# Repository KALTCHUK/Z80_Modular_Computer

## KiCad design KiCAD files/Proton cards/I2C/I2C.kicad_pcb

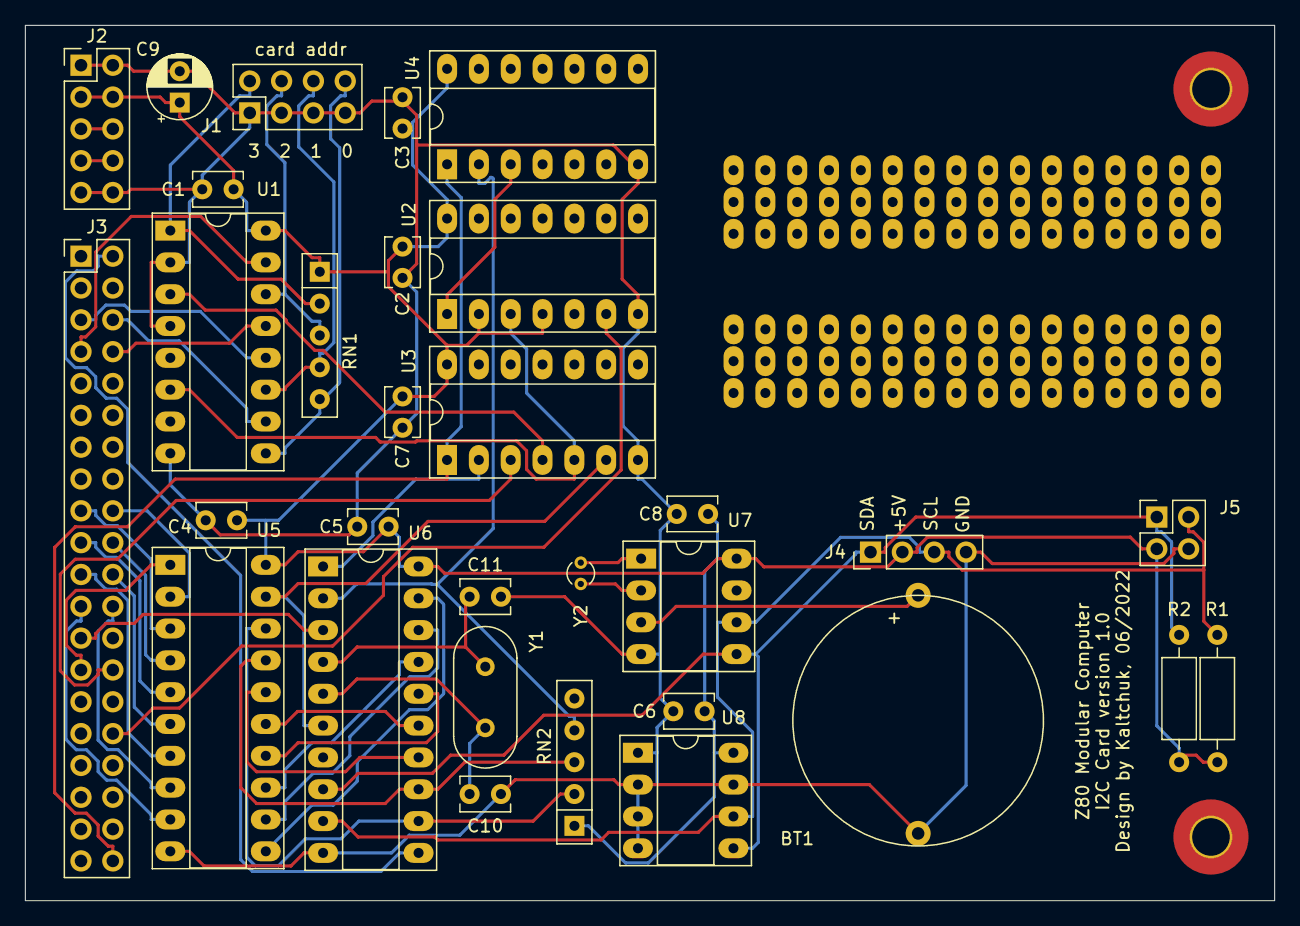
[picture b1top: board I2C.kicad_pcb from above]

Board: 2 copper layers, 99.7 x 69.8 mm, 33 parts (0 on the bottom side), 47 nets.

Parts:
BT1: 3V; Battery-Holder_CR2032
C1, C2, C3, C4, C5, C6, C7, C8: 10nF; C_Disc_D3.8mm_W2.6mm_P2.50mm
C9: 10uF; CP_Radial_D5.0mm_P2.50mm
C10, C11: 33pF; C_Disc_D3.8mm_W2.6mm_P2.50mm
H1, H2: MountingHole; MountingHole_3mm_Pad_TopBottom
J1: card addr; PinHeader_2x04_P2.54mm_Vertical
J2: Power Bus; PinHeader_2x05_P2.54mm_Vertical
J3: Signal Bus; PinHeader_2x20_P2.54mm_Vertical
J4: I2C int; PinHeader_1x04_P2.54mm_Vertical
J5: I2C ext; PinHeader_2x02_P2.54mm_Vertical
R1, R2: 6k8; R_Axial_DIN0207_L6.3mm_D2.5mm_P10.16mm_Horizontal
RN1, RN2: 4x10k; R_Array_SIP5
U1: 74LS85; DIP-16_W7.62mm_Socket_LongPads
U2: 74LS74; DIP-14_W7.62mm_Socket_LongPads
U3: 74LS04; DIP-14_W7.62mm_Socket_LongPads
U4: 74LS08; DIP-14_W7.62mm_Socket_LongPads
U5: 74LS245; DIP-20_W7.62mm_Socket_LongPads
U6: AT89C4051-24P; DIP-20_W7.62mm_Socket_LongPads
U7: DS1307+; DIP-8_W7.62mm_Socket_LongPads
U8: FM24C64B; DIP-8_W7.62mm_Socket_LongPads
Y1: 24MHz; Crystal_HC49-U_Vertical
Y2: 32.768kHz; Crystal_Round_D1.5mm_Vertical

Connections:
+5V: C1.1, C2.1, C3.1, C4.1, C5.1, C6.1, C7.1, C8.1, C9.1, J2.3, J2.4, J4.2, J5.3, R1.2, R2.2, RN1.1 (common), RN2.1 (common), U1.16 (VCC), U2.2 (D), U2.4 (~S), U2.14 (VCC), U3.14 (VCC), U4.14 (VCC), U5.20 (VCC), U6.20 (VCC), U7.8 (VCC), U8.8 (VDD)
+12V: J2.5, J2.6
+BATT: BT1.1 (+), U7.3 (VBAT)
/B00: RN2.2 (R1), U5.18 (B0), U6.12 (P1.0)
/B01: RN2.3 (R2), U5.17 (B1), U6.13 (P1.1)
/B02: U5.16 (B2), U6.14 (P1.2)
/B03: U5.15 (B3), U6.15 (P1.3)
/B04: U5.14 (B4), U6.16 (P1.4)
/B05: U5.13 (B5), U6.17 (P1.5)
/B06: U5.12 (B6), U6.18 (P1.6)
/B07: U5.11 (B7), U6.19 (P1.7)
/SCL: J4.3, J5.2, R1.1, U6.9 (P3.5), U7.6 (SCL), U8.6 (SCL)
/SDA: J4.1, J5.1, R2.1, U6.8 (P3.4), U7.5 (SDA), U8.5 (SDA)
/a00: J3.2, U6.11 (P3.7)
/a04: J3.6, U1.10 (A0)
/a05: J3.5, U1.12 (A1)
/a06: J3.8, U1.13 (A2)
/a07: J3.7, U1.15 (A3)
/card_sel: U1.6 (Oa=b), U2.3 (C), U3.5
/d00: J3.18, U5.2 (A0)
/d01: J3.17, U5.3 (A1)
/d02: J3.20, U5.4 (A2)
/d03: J3.19, U5.5 (A3)
/d04: J3.22, U5.6 (A4)
/d05: J3.21, U5.7 (A5)
/d06: J3.24, U5.8 (A6)
/d07: J3.23, U5.9 (A7)
/iorq: J3.28, U3.3
/rd: J3.27, U5.1 (A->B)
/reset: J3.40, U3.1, U4.1
/v1: J2.7, J2.8
/wait: J3.32, U2.6 (~Q)
/wr: J3.25, U6.3 (P3.1)
GND: BT1.2 (-), C1.2, C2.2, C3.2, C4.2, C5.2, C6.2, C7.2, C8.2, C9.2, C10.2, C11.2, J1.1, J1.3, J1.5, J1.7, J2.1, J2.2, J2.9, J2.10, J4.4, J5.4, U1.2 (Ia<b), U1.4 (Ia>b), U1.8 (GND), U2.7 (GND), U3.7 (GND), U4.7 (GND), U5.10 (GND), U6.10 (GND), U7.4 (GND), U8.1 (A0), U8.2 (A1), U8.3 (A2), U8.4 (VSS), U8.7 (WP)
unnamed: C10.1, U6.5 (XTAL1), Y1.2
unnamed: C11.1, U6.4 (XTAL2), Y1.1
unnamed: J1.2, RN1.2 (R1), U1.1 (B3)
unnamed: J1.4, RN1.3 (R2), U1.14 (B2)
unnamed: J1.6, RN1.4 (R3), U1.11 (B1)
unnamed: J1.8, RN1.5 (R4), U1.9 (B0)
unnamed: RN2.4 (R3), U4.2, U6.2 (P3.0)
unnamed: U1.3 (Ia=b), U3.4
unnamed: U2.1 (~R), U4.3
unnamed: U3.2, U6.1 (RST/VPP)
unnamed: U3.6, U5.19 (CE), U6.6 (P3.2)
unnamed: U7.1 (X1), Y2.2
unnamed: U7.2 (X2), Y2.1

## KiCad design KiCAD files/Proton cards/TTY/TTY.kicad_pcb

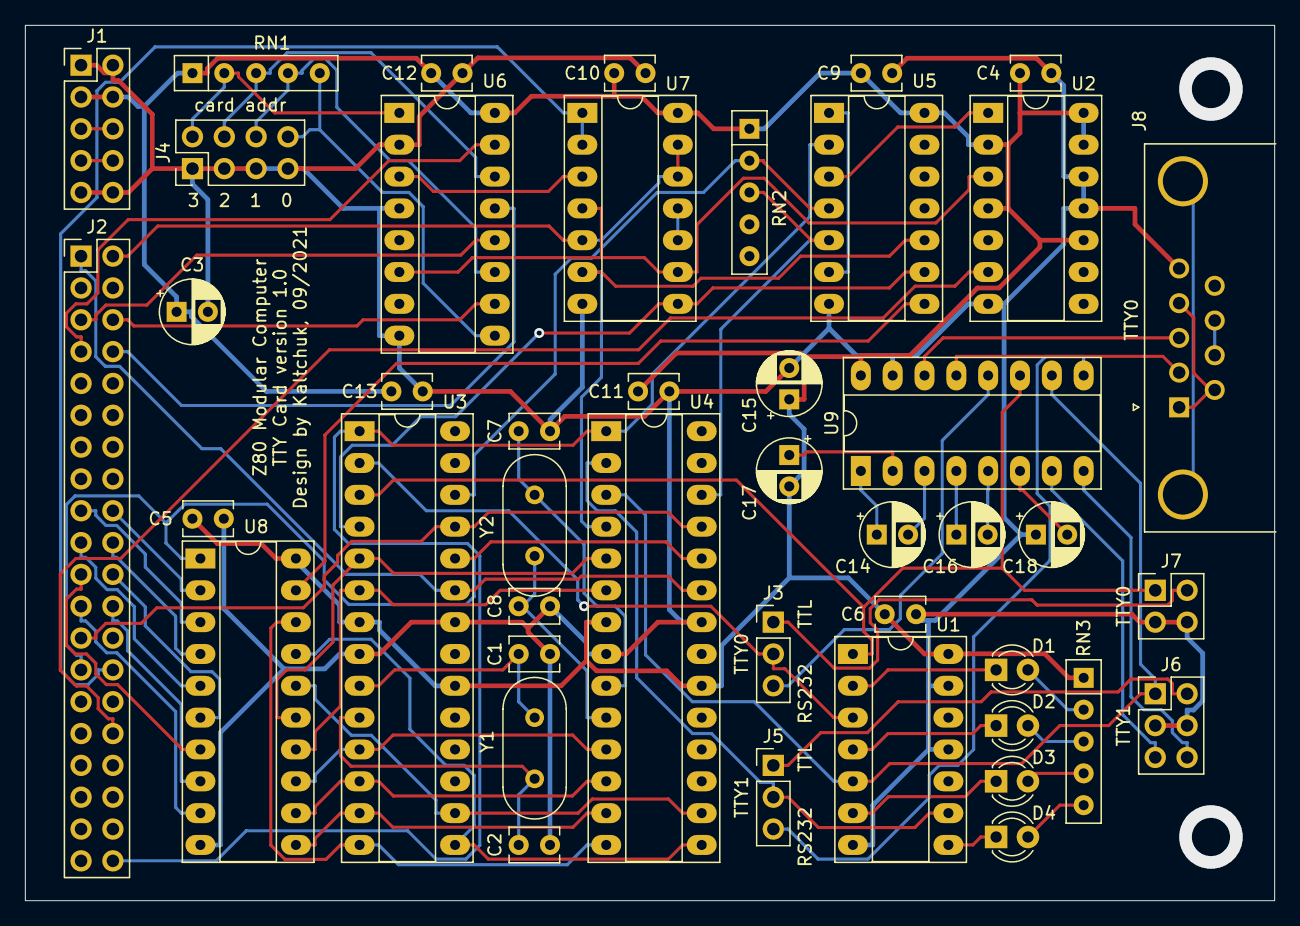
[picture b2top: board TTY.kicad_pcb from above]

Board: 2 copper layers, 99.7 x 69.9 mm, 44 parts (0 on the bottom side), 77 nets.

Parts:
C1, C2, C7, C8: 22pF; C_Disc_D3.8mm_W2.6mm_P2.50mm
C3: 10uF; CP_Radial_D5.0mm_P2.50mm
C4, C5, C6, C9, C10, C11, C12, C13: 10nF; C_Disc_D3.8mm_W2.6mm_P2.50mm
C14, C15, C16, C17, C18: 1uF; CP_Radial_D5.0mm_P2.50mm
D1, D2, D3, D4: LED; LED_D3.0mm
J1: Power Bus; PinHeader_2x05_P2.54mm_Vertical
J2: Signal Buss; PinHeader_2x20_P2.54mm_Vertical
J3, J5: TTL/RS232; PinHeader_1x03_P2.54mm_Vertical
J4: Card addr; PinHeader_2x04_P2.54mm_Vertical
J6: TTY1; PinHeader_2x03_P2.54mm_Vertical
J7: TTY0; PinHeader_2x02_P2.54mm_Vertical
J8: DB9; DSUB-9_Male_Horizontal_P2.77x2.84mm_EdgePinOffset4.94mm_Hou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
RN1, RN2: 4x10k; R_Array_SIP5
RN3: 4x220; R_Array_SIP5
U1: 74LS07; DIP-14_W7.62mm_Socket_LongPads
U2: 74LS74; DIP-14_W7.62mm_Socket_LongPads
U3, U4: ATmega328P-PU; DIP-28_W7.62mm_Socket_LongPads
U5: 74LS08; DIP-14_W7.62mm_Socket_LongPads
U6: 74LS85; DIP-16_W7.62mm_Socket_LongPads
U7: 74LS00; DIP-14_W7.62mm_Socket_LongPads
U8: 74LS245; DIP-20_W7.62mm_Socket_LongPads
U9: MAX232; DIP-16_W7.62mm_Socket_LongPads
Y1, Y2: 20MHz; Crystal_HC49-U_Vertical

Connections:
+5V: C3.1, C4.1, C5.1, C6.1, C9.1, C10.1, C11.1, C12.1, C13.1, C15.1, C17.2, J1.3, J1.4, RN1.1, RN2.1, RN3.1, U1.14, U2.2, U2.4, U2.10, U2.13, U2.14, U3.7, U3.20, U4.7, U4.20, U5.14, U6.16, U7.14, U8.20, U9.16
/+12V: J1.5, J1.6
/B00: U3.14, U4.14, U8.18
/B01: U3.15, U4.15, U8.17
/B02: U3.16, U4.16, U8.16
/B03: U3.5, U4.5, U8.15
/B04: U3.6, U4.6, U8.14
/B05: U3.11, U4.11, U8.13
/B06: U3.12, U4.12, U8.12
/B07: U3.13, U4.13, U8.11
/CS0: U3.4, U5.9, U7.8
/CS1: U4.4, U5.10, U7.6
/RSM0: RN2.2, U3.26, U5.4
/RSM1: RN2.3, U4.26, U5.5
/RX0: J3.2, U1.3, U3.2
/RX0RS232: J3.3, U9.12
/RX0TTL: J3.1, J7.2
/RX1: J5.2, U1.9, U4.2
/RX1RS232: J5.3, U9.9
/RX1TTL: J5.1, J6.2
/TX0: J7.1, U1.1, U3.3, U9.11
/TX1: J6.1, U1.5, U4.3, U9.10
/a00: J2.2, U7.5, U7.12, U7.13
/a01: J2.1, U3.23, U4.23
/a04: J2.6, U6.10
/a05: J2.5, U6.12
/a06: J2.8, U6.13
/a07: J2.7, U6.15
/d00: J2.18, U8.2
/d01: J2.17, U8.3
/d02: J2.20, U8.4
/d03: J2.19, U8.5
/d04: J2.22, U8.6
/d05: J2.21, U8.7
/d06: J2.24, U8.8
/d07: J2.23, U8.9
/iorq: J2.28, U7.1, U7.2
/rd: J2.27, U3.24, U4.24, U8.1
/reset: J2.40, U3.1, U4.1, U5.2
/v1: J1.7, J1.8
/wait: J2.32, U2.6
/wr: J2.25, U3.25, U4.25
GND: C1.2, C2.2, C3.2, C4.2, C5.2, C6.2, C7.2, C8.2, C9.2, C10.2, C11.2, C12.2, C13.2, C15.2, C18.1, J1.1, J1.2, J1.9, J1.10, J4.1, J4.3, J4.5, J4.7, J6.3, J6.4, J7.3, J7.4, J8.5, U1.7, U1.11, U1.13, U2.7, U2.11, U2.12, U3.8, U3.22, U4.8, U4.22, U5.7, U6.2, U6.4, U6.8, U7.7, U8.10, U9.15
unnamed: C1.1, U3.9, Y1.1
unnamed: C2.1, U3.10, Y1.2
unnamed: C7.1, U4.9, Y2.1
unnamed: C8.1, U4.10, Y2.2
unnamed: C14.1, U9.1
unnamed: C14.2, U9.3
unnamed: C16.1, U9.4
unnamed: C16.2, U9.5
unnamed: C17.1, U9.2
unnamed: C18.2, U9.6
unnamed: D1.1, U1.2
unnamed: D1.2, RN3.2
unnamed: D2.1, U1.4
unnamed: D2.2, RN3.3
unnamed: D3.1, U1.6
unnamed: D3.2, RN3.4
unnamed: D4.1, U1.8
unnamed: D4.2, RN3.5
unnamed: J4.2, RN1.2, U6.1
unnamed: J4.4, RN1.3, U6.14
unnamed: J4.6, RN1.4, U6.11
unnamed: J4.8, RN1.5, U6.9
unnamed: J6.5, U9.7
unnamed: J6.6, U9.8
unnamed: J8.1, J8.4, J8.6
unnamed: J8.2, U9.13
unnamed: J8.3, U9.14
unnamed: J8.7, J8.8
unnamed: U2.1, U5.3
unnamed: U2.3, U6.6, U7.4, U7.9
unnamed: U5.1, U5.6
unnamed: U5.8, U8.19
unnamed: U6.3, U7.3
unnamed: U7.10, U7.11

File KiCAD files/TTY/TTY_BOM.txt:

C1, C2, C7, C8	22pF	Capacitor_THT:C_Disc_D3.8mm_W2.6mm_P2.50mm	~	4
        C1	22pF	Capacitor_THT:C_Disc_D3.8mm_W2.6mm_P2.50mm	~	1
        C2	22pF	Capacitor_THT:C_Disc_D3.8mm_W2.6mm_P2.50mm	~	1
        C7	22pF	Capacitor_THT:C_Disc_D3.8mm_W2.6mm_P2.50mm	~	1
        C8	22pF	Capacitor_THT:C_Disc_D3.8mm_W2.6mm_P2.50mm	~	1
    C3	10uF	Capacitor_THT:CP_Radial_D5.0mm_P2.50mm	~	1
  C4-C6, C9-C13	10nF	Capacitor_THT:C_Disc_D3.8mm_W2.6mm_P2.50mm	~	8
  C14-C18	1uF	Capacitor_THT:CP_Radial_D5.0mm_P2.50mm	~	5
  D1-D4	LED	LED_THT:LED_D3.0mm	~	4
    J1	Power Bus	Connector_PinHeader_2.54mm:PinHeader_2x05_P2.54mm_Vertical	~	1
    J2	Signal Buss	Connector_PinHeader_2.54mm:PinHeader_2x20_P2.54mm_Vertical	~	1
  J3, J5	TTL/RS232	Connector_PinHeader_2.54mm:PinHeader_1x03_P2.54mm_Vertical	~	2
    J4	Card addr	Connector_PinHeader_2.54mm:PinHeader_2x04_P2.54mm_Vertical	~	1
    J6	TTY1	Connector_PinHeader_2.54mm:PinHeader_2x03_P2.54mm_Vertical	~	1
    J7	TTY0	Connector_PinHeader_2.54mm:PinHeader_2x02_P2.54mm_Vertical	~	1
    J8	DB9	Connector_Dsub:DSUB-9_Male_Horizontal_P2.77x2.84mm_EdgePinOffset4.94mm_Housed_MountingHolesOffset7.48mm	 ~	1
  RN1, RN2	4x10k	Resistor_THT:R_Array_SIP5	http://www.vishay.com/docs/31509/csc.pdf	2
    RN3	4x220	Resistor_THT:R_Array_SIP5	http://www.vishay.com/docs/31509/csc.pdf	1
    U1	74LS07	Package_DIP:DIP-14_W7.62mm_Socket_LongPads	www.ti.com/lit/ds/symlink/sn74ls07.pdf	1
    U2	74LS74	Package_DIP:DIP-14_W7.62mm_Socket_LongPads	74xx/74hc_hct74.pdf	1
  U3, U4	ATmega328P-PU	Package_DIP:DIP-28_W7.62mm_Socket_LongPads	http://ww1.microchip.com/downloads/en/DeviceDoc/ATmega328_P%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	2
    U5	74LS08	Package_DIP:DIP-14_W7.62mm_Socket_LongPads	http://www.ti.com/lit/gpn/sn74LS08	1
    U6	74LS85	Package_DIP:DIP-16_W7.62mm_Socket_LongPads	http://www.ti.com/lit/gpn/sn74LS85	1
    U7	74LS00	Package_DIP:DIP-14_W7.62mm_Socket_LongPads	http://www.ti.com/lit/gpn/sn74ls00	1
    U8	74LS245	Package_DIP:DIP-20_W7.62mm_Socket_LongPads	http://www.ti.com/lit/gpn/sn74LS245	1
    U9	MAX232	Package_DIP:DIP-16_W7.62mm_Socket_LongPads	http://www.ti.com/lit/ds/symlink/max232.pdf	1
  Y1, Y2	20MHz	Crystal:Crystal_HC49-U_Vertical	~	2
